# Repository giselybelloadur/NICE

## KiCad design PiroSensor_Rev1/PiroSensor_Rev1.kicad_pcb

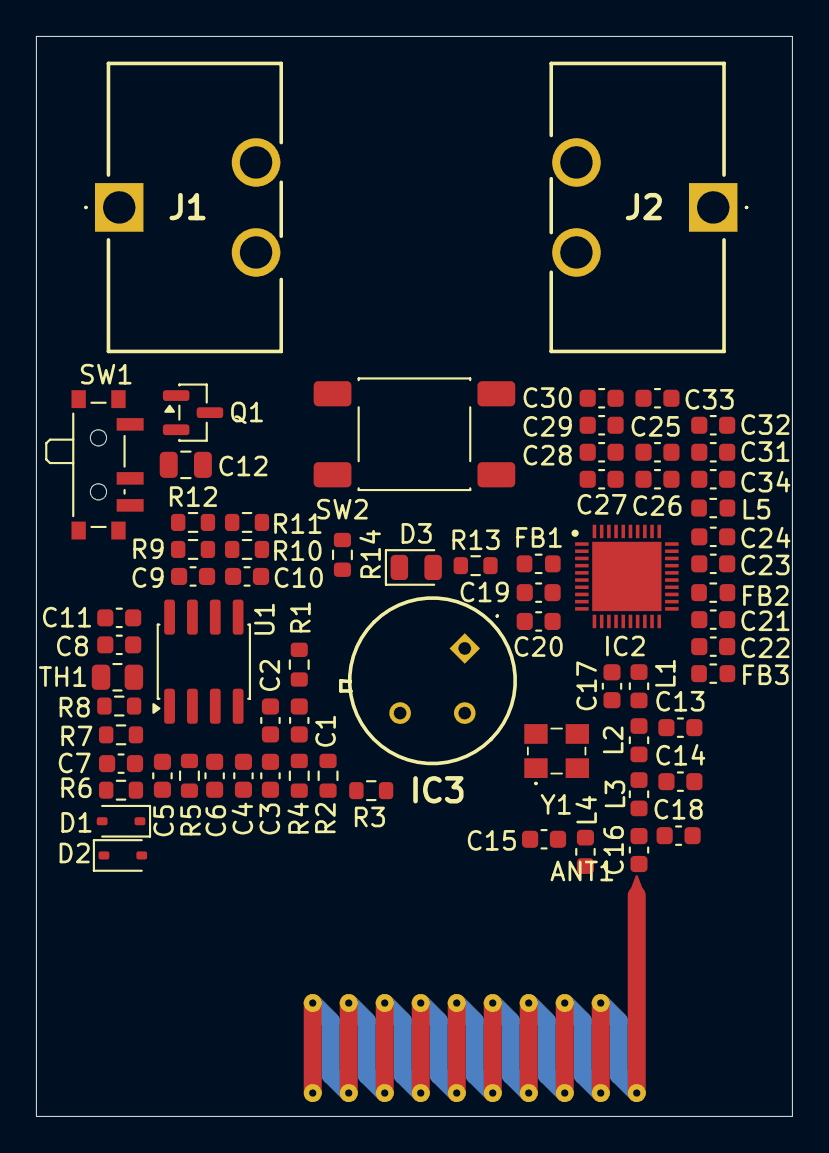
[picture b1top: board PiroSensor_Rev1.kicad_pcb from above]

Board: 2 copper layers, 42.0 x 60.0 mm, 70 parts (0 on the bottom side), 34 nets, no tracks yet.

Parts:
ANT1: ANT_902-930MHz_BR; Meander_902-930MHz_BR
C1, C2, C3, C4, C5, C6, C7, C8, C9, C10, C11, C27: 10nF; C_0603_1608Metric
C12: C; C_0805_2012Metric
C13, C15: C; C_0603_1608Metric
C14: 7,2pF; C_0603_1608Metric
C16: 220pF; C_0603_1608Metric
C17: 1,9pF; C_0603_1608Metric
C18: 1,3pF; C_0603_1608Metric
C19, C28, C30, C32: 1uF; C_0603_1608Metric
C20, C22: 100pF; C_0603_1608Metric
C21: 470nF; C_0603_1608Metric
C23, C24: 1,5pF; C_0603_1608Metric
C25: 10uF; C_0603_1608Metric
C26, C29, C31, C33: 100nF; C_0603_1608Metric
C34: 4,7uF; C_0603_1608Metric
D1, D2: LL4148; D_SOD-323
D3: LED; LED_0805_2012Metric
FB1, FB2, FB3: FerriteBead; L_0603_1608Metric
IC2: EFR32FG23L020F128GM40-C; QFN40P500X500X90-41N-D
IC3: PYD1398
J1, J2: MY-18650-01; MY1865001
L1: 1,5nH; L_0603_1608Metric
L2: 1,3nH; L_0603_1608Metric
L3: 13nH; L_0603_1608Metric
L4: 18nH; L_0603_1608Metric
L5: 2,2uH; L_0603_1608Metric
Q1: AO3401A; SOT-23
R1, R4, R5, R6, R7, R8, R9, R10, R11, R13: 100K; R_0603_1608Metric
R2, R3, R12: 0R; R_0603_1608Metric
R14: R_US; R_0603_1608Metric
SW1: SW_SPDT; SW_SPDT_PCM12
SW2: SW_Push; SW_Push_1P1T_NO_E-Switch_TL3301NxxxxxG
TH1: Thermistor_NTC; R_0805_2012Metric
U1: LM358; SOIC-8_3.9x4.9mm_P1.27mm
Y1: 39MHz; ABM8AIG25000MHZ122ZT3

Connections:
+3V0: C11.2, C12.1, C25.1, C26.1, C27.1, C28.1, C29.1, C30.1, C33.1, C34.1, FB1.1, FB2.1, IC2.32 (VREGVDD), IC2.34 (DVDD), IC2.35 (AVDD), IC2.36 (IOVDD), L5.1, R1.1, R11.2, R14.1, SW1.3 (C), U1.8 (V+)
GND: C1.2, C2.2, C3.2, C4.2, C5.2, C6.2, C10.1, C11.1, C12.2, C13.2, C14.2, C15.2, C18.2, C19.2, C20.2, C21.2, C22.2, C23.2, C24.2, C25.2, C26.2, C27.2, C28.2, C29.2, C30.2, C31.2, C32.2, C33.2, C34.2, D3.1 (K), IC2.13 (RFVSS), IC2.33 (VREGVSS), IC2.41 (EP), IC3.1 (G), J2.1, J2.2, J2.3, Q1.1 (G), R4.2, R10.1, SW2.1, U1.4 (V-), Y1.2 (GND_1), Y1.4 (GND_2)
LED_PIR1: IC2.22 (PA01), R13.1
unnamed: ANT1.1 (FEED_1), C16.2, L4.2
unnamed: C6.1, R5.2
unnamed: C8.2, R8.1, TH1.1
unnamed: C9.1, R9.1, R12.2, U1.7
unnamed: C13.1, C17.2, L1.2, L2.1
unnamed: C14.1, L2.2, L3.1
unnamed: C16.1, C18.1, L3.2
unnamed: C21.1, C22.1, FB2.2, FB3.1
unnamed: C5.1, C7.2, D1.2 (A), D2.1 (K), R5.1, R6.2, U1.2 (-)
unnamed: C7.1, D1.1 (K), D2.2 (A), R6.1, R7.2, U1.1
unnamed: D3.2 (A), R13.2
unnamed: C31.1, C32.1, IC2.30 (DECOUPLE)
unnamed: IC2.9 (HFXTAL_I), Y1.1 (X1)
unnamed: IC2.10 (HFXTAL_O), Y1.3 (X2)
unnamed: FB3.2, IC2.18 (PAVDD)
unnamed: C19.1, C20.1, FB1.2, IC2.12 (RFVDD)
unnamed: C15.1, IC2.15 (SUBG_I0), L4.1
unnamed: C24.1, IC2.14 (SUBG_I1)
unnamed: C17.1, IC2.17 (SUBG_O0), L1.1
unnamed: C23.1, IC2.16 (SUBG_O1)
unnamed: IC2.31 (VREGSW), L5.2
unnamed: C1.1, C2.1, IC3.3 (D), R1.2
unnamed: IC3.2 (S), R2.2, R3.2
unnamed: J1.1, J1.2, J1.3, Q1.3 (D)
unnamed: Q1.2 (S), SW1.2 (B)
unnamed: R7.1, R8.2, TH1.2
unnamed: C3.1, C4.1, R2.1, R4.1, U1.3 (+)
unnamed: C10.2, R10.2, R11.1, U1.5 (+)
unnamed: C8.1, C9.2, R9.2, U1.6 (-)
PIR1: IC2.21 (PA00), R3.1, R12.1
TECLA: IC2.23 (PA02), R14.2, SW2.2

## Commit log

2026-06-04 feat: inicialização do projeto PiroSensor_Rev1
2026-06-04 feat: atualização do projeto - 2026-06-04 13:06
2026-06-04 feat: atualização do projeto - 2026-06-04 19:33
2026-06-05 feat: atualização do projeto - 2026-06-05 15:12
